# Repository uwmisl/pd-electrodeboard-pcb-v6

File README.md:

# pd-electrodeboard-v6

Electrode board designed for 5 reservoir + 4 pumped inputs with non-homegenous electrode sizes.

## Automated generation

Footprints and layout.yml file for [kicad component layout plugin](https://github.com/mcbridejc/kicad_component_layout)
are generated by scripted_layout_v6.py.

Fiducial footprints are generated by create_fiducial_footprints.py.

## Changelog

### Revision 6.2

- Changes to smaller crenellation
- Changes reservoir shapes: flat tiered instead of chevrons.

### Revision 6.1

- Shrinks total height of the board to 75mm, and y-delta between mounting holes to 64mm.
- Increases the size of the fiducials from 6mm to 8mm.
- Updates chevron reservoirs with crenellated edges

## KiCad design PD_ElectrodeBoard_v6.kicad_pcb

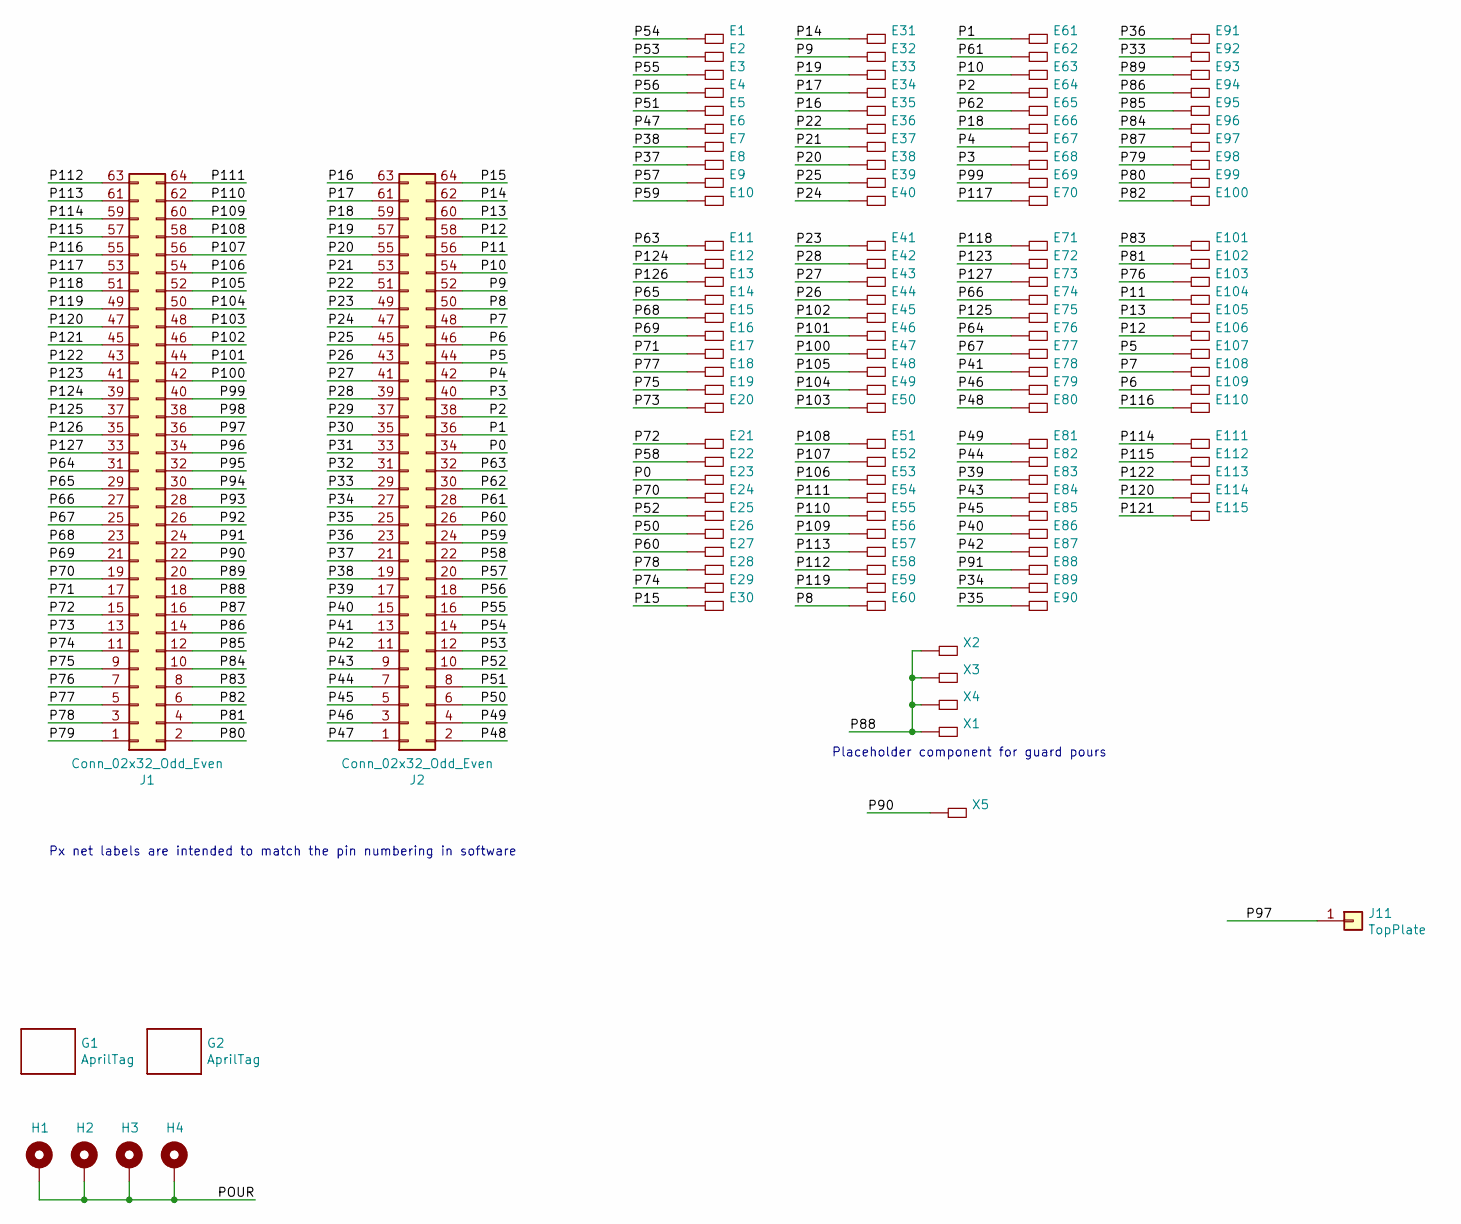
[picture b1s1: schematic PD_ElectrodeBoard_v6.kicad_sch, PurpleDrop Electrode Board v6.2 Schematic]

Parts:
E1, E2, E3, E4, E5, E6, E7, E8, E9, E10, E11, E12, E13, E14, E15, E16, E17, E18, E19, E20, E21, E22, E23, E24, E25, E26, E27, E28, E29, E30, E31, E32, E33, E34, E35, E36, E37, E38, E39, E40, E41, E42, E43, E44, E45, E46, E47, E48, E49, E50, E51, E52, E53, E54, E55, E56, E57, E58, E59, E60, E61, E62, E63, E64, E65, E66, E67, E68, E69, E70, E71, E72, E73, E74, E75, E76, E77, E78, E79, E80, E81, E82, E83, E84, E85, E86, E87, E88, E89, E90, E91, E92, E93, E94, E95, E96, E97, E98, E99, E100, E101, E102, E103, E104, E105, E106, E107, E108, E109, E110, E111, E112, E113, E114, E115: DMFElectrode; electrode_E1
G1: AprilTag; tag36_11_00011_8.00mm
G2: AprilTag; tag36_11_00012_8.00mm
H1, H2, H3, H4: MountingHole_Pad; Keystone-4929
J1, J2: Conn_02x32_Odd_Even; CLP-132-02-F-D
J11: TopPlate; Header1_RA
X1, X2, X3, X4, X5: DMFElectrode; SimplePad

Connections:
/P0: E23.1, J2.34
/P1: E61.1, J2.36
/P2: E64.1, J2.38
/P3: E68.1, J2.40
/P4: E67.1, J2.42
/P5: E107.1, J2.44
/P6: E109.1, J2.46
/P7: E108.1, J2.48
/P8: E60.1, J2.50
/P9: E32.1, J2.52
/P10: E63.1, J2.54
/P11: E104.1, J2.56
/P12: E106.1, J2.58
/P13: E105.1, J2.60
/P14: E31.1, J2.62
/P15: E30.1, J2.64
/P16: E35.1, J2.63
/P17: E34.1, J2.61
/P18: E66.1, J2.59
/P19: E33.1, J2.57
/P20: E38.1, J2.55
/P21: E37.1, J2.53
/P22: E36.1, J2.51
/P23: E41.1, J2.49
/P24: E40.1, J2.47
/P25: E39.1, J2.45
/P26: E44.1, J2.43
/P27: E43.1, J2.41
/P28: E42.1, J2.39
/P29: J2.37
/P30: J2.35
/P31: J2.33
/P32: J2.31
/P33: E92.1, J2.29
/P34: E89.1, J2.27
/P35: E90.1, J2.25
/P36: E91.1, J2.23
/P37: E8.1, J2.21
/P38: E7.1, J2.19
/P39: E83.1, J2.17
/P40: E86.1, J2.15
/P41: E78.1, J2.13
/P42: E87.1, J2.11
/P43: E84.1, J2.9
/P44: E82.1, J2.7
/P45: E85.1, J2.5
/P46: E79.1, J2.3
/P47: E6.1, J2.1
/P48: E80.1, J2.2
/P49: E81.1, J2.4
/P50: E26.1, J2.6
/P51: E5.1, J2.8
/P52: E25.1, J2.10
/P53: E2.1, J2.12
/P54: E1.1, J2.14
/P55: E3.1, J2.16
/P56: E4.1, J2.18
/P57: E9.1, J2.20
/P58: E22.1, J2.22
/P59: E10.1, J2.24
/P60: E27.1, J2.26
/P61: E62.1, J2.28
/P62: E65.1, J2.30
/P63: E11.1, J2.32
/P64: E76.1, J1.31
/P65: E14.1, J1.29
/P66: E74.1, J1.27
/P67: E77.1, J1.25
/P68: E15.1, J1.23
/P69: E16.1, J1.21
/P70: E24.1, J1.19
/P71: E17.1, J1.17
/P72: E21.1, J1.15
/P73: E20.1, J1.13
/P74: E29.1, J1.11
/P75: E19.1, J1.9
/P76: E103.1, J1.7
/P77: E18.1, J1.5
/P78: E28.1, J1.3
/P79: E98.1, J1.1
/P80: E99.1, J1.2
/P81: E102.1, J1.4
/P82: E100.1, J1.6
/P83: E101.1, J1.8
/P84: E96.1, J1.10
/P85: E95.1, J1.12
/P86: E94.1, J1.14
/P87: E97.1, J1.16
/P88: J1.18, X1.1, X2.1, X3.1, X4.1
/P89: E93.1, J1.20
/P90: J1.22, X5.1
/P91: E88.1, J1.24
/P92: J1.26
/P93: J1.28
/P94: J1.30
/P95: J1.32
/P96: J1.34
/P97: J1.36, J11.1
/P98: J1.38
/P99: E69.1, J1.40
/P100: E47.1, J1.42
/P101: E46.1, J1.44
/P102: E45.1, J1.46
/P103: E50.1, J1.48
/P104: E49.1, J1.50
/P105: E48.1, J1.52
/P106: E53.1, J1.54
/P107: E52.1, J1.56
/P108: E51.1, J1.58
/P109: E56.1, J1.60
/P110: E55.1, J1.62
/P111: E54.1, J1.64
/P112: E58.1, J1.63
/P113: E57.1, J1.61
/P114: E111.1, J1.59
/P115: E112.1, J1.57
/P116: E110.1, J1.55
/P117: E70.1, J1.53
/P118: E71.1, J1.51
/P119: E59.1, J1.49
/P120: E114.1, J1.47
/P121: E115.1, J1.45
/P122: E113.1, J1.43
/P123: E72.1, J1.41
/P124: E12.1, J1.39
/P125: E75.1, J1.37
/P126: E13.1, J1.35
/P127: E73.1, J1.33
/POUR: H1.1, H2.1, H3.1, H4.1

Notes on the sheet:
Placeholder component for guard pours
Px net labels are intended to match the pin numbering in software

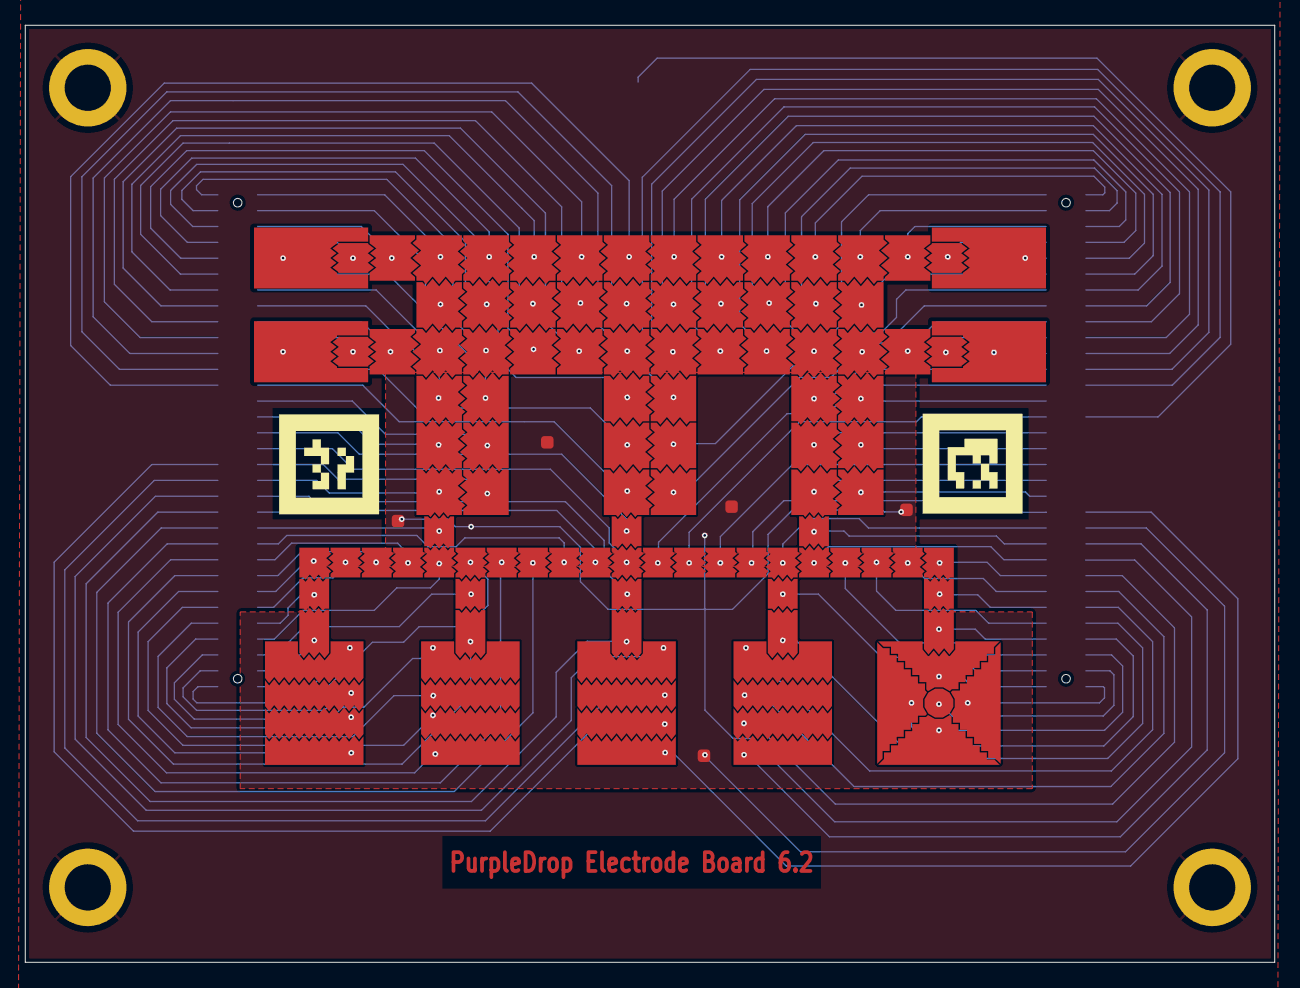
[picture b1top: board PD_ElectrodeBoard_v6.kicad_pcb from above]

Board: 2 copper layers, 100.0 x 75.0 mm, 129 parts (1 on the bottom side), 119 nets.

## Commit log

2021-03-11 Initial commit of mostly routed board
    Still needs some review and cleanup
2021-03-15 Finished layout
2021-03-18 update layout generation to generate the board description JSON
2021-04-15 Rev 6.1 update
2022-02-24 Design 6.2

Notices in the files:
parts and their libraries:
Copyright 2016 Accelerated Designs. All rights reserved.
